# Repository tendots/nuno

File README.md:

# nuno
Electric fabric touchsensor module "nüno"

導電布タッチセンサーモジュールnünoのコードです。

質問や要望などあればこのページかFacebookページへご連絡ください。
* Facebook page https://www.facebook.com/Project-n%C3%BCno-183796265747425/

## 仕様 ##
* 静電容量タッチセンサ　[mtch6102](https://www.microchip.com/wwwproducts/en/MTCH6102)
* タッチチャンネル数8
* コネクタ GROVEコネクタ(I2C)

## 導線部接続方法

導線部（細長い方）は画像のように、縫い目がセンサー部（四角い方）の外縁に向くように接続してください。
逆につけた取り付けた場合、すべてのチャンネルの値が取得できません。

## フレキシブル基板コネクタ接続方法 ##

フレキシブル基板のコネクタは、リジット基板のFPCコネクタに接続後、
画像のようにフレキシブル基板と布を両方挟み込むようにして、
付属の固定具でネジ止めしてください。

## 付属ケースカット方法 ##

## 参考 ##
[touch_timer](https://github.com/theapi/touch_timer)

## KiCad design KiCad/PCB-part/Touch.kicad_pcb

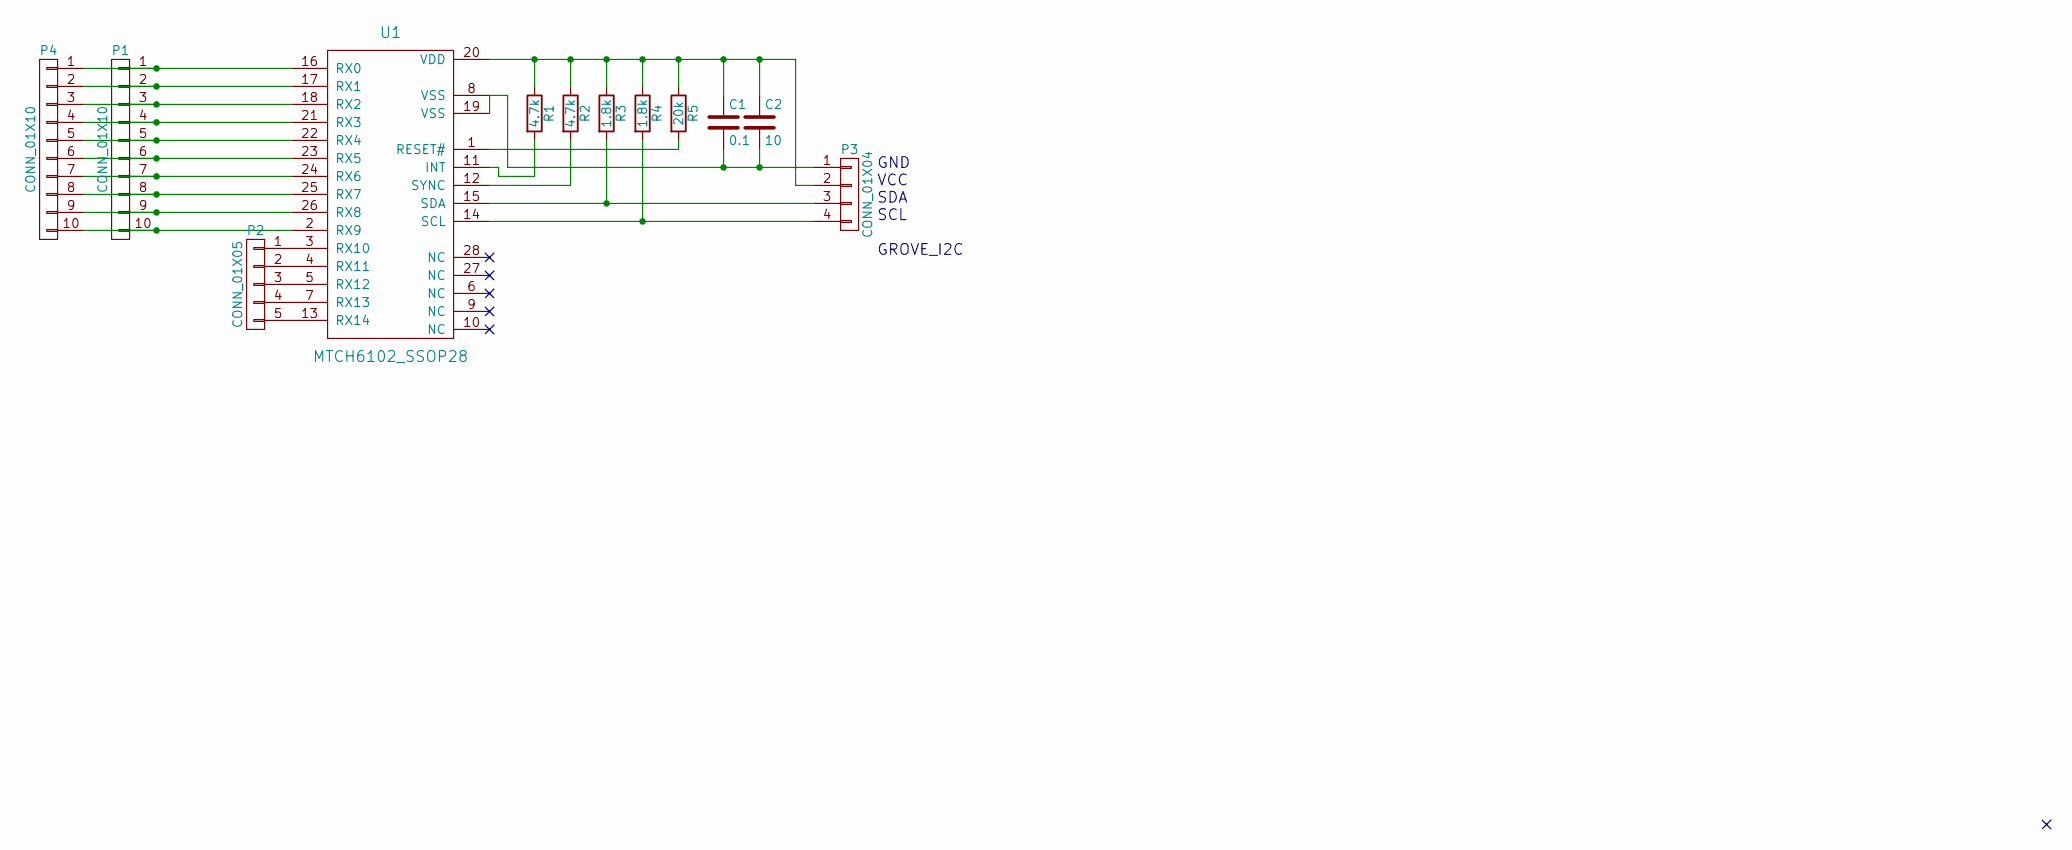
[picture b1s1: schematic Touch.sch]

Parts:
C1: 0.1; C_0603
C2: 10; C_0603
P1: CONN_01X10; Connector_Molex_PicoBlade_53047-1010
P2: CONN_01X05; Connector_Molex_PicoBlade_53047-0510
P3: CONN_01X04; Grove_I2C_Horisontal_4pin_2mmpitch
P4: CONN_01X10; FFC_CONNECTOR_1.0D-WTS-10P
R1, R2: 4.7k; R_0603
R3, R4: 1.8k; R_0603
R5: 20k; R_0603
U1: MTCH6102_SSOP28; SSOP-28_5.3x10.2mm_Pitch0.65mm

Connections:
unnamed: C1.1, C2.1, P3.2, R1.1, R2.1, R3.1, R4.1, R5.1, U1.20 (VDD)
unnamed: C1.2, C2.2, P3.1, U1.8 (VSS), U1.19 (VSS)
unnamed: P1.1, P4.1, U1.16 (RX0)
unnamed: P1.2, P4.2, U1.17 (RX1)
unnamed: P1.3, P4.3, U1.18 (RX2)
unnamed: P1.4, P4.4, U1.21 (RX3)
unnamed: P1.5, P4.5, U1.22 (RX4)
unnamed: P1.6, P4.6, U1.23 (RX5)
unnamed: P1.7, P4.7, U1.24 (RX6)
unnamed: P1.8, P4.8, U1.25 (RX7)
unnamed: P1.9, P4.9, U1.26 (RX8)
unnamed: P1.10, P4.10, U1.2 (RX9)
unnamed: P2.1, U1.3 (RX10)
unnamed: P2.2, U1.4 (RX11)
unnamed: P2.3, U1.5 (RX12)
unnamed: P2.4, U1.7 (RX13)
unnamed: P2.5, U1.13 (RX14)
unnamed: P3.3, R3.2, U1.15 (SDA)
unnamed: P3.4, R4.2, U1.14 (SCL)
unnamed: R1.2, U1.11 (INT)
unnamed: R2.2, U1.12 (SYNC)
unnamed: R5.2, U1.1 (RESET#)

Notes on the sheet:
GND VCC SDA SCL GROVE_I2C

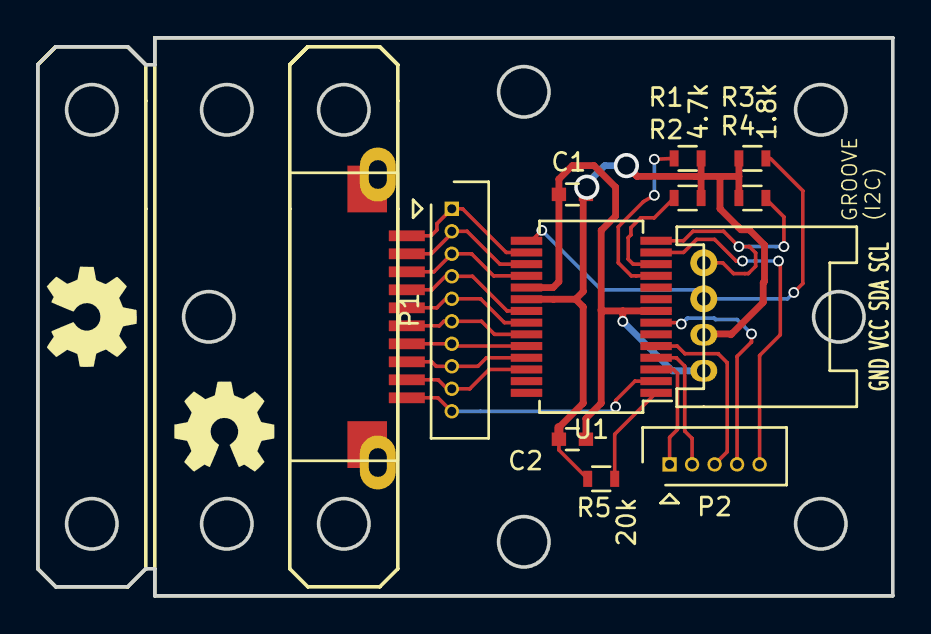
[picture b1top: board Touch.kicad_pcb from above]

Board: 2 copper layers, 47.5 x 31.0 mm, 14 parts (0 on the bottom side), 22 nets.

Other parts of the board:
OSHW: 1.1; OSHW_LOGL_SYLK_5mm
OSHW#2: 1.1; OSHW_LOGL_SYLK_5mm

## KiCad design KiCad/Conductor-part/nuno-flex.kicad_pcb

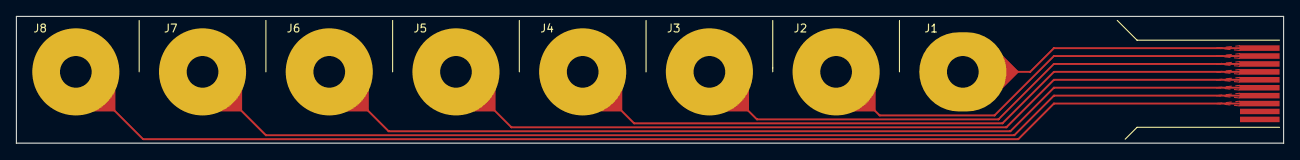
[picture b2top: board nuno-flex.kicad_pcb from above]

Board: 2 copper layers, 160.0 x 16.0 mm, 9 parts (0 on the bottom side), 8 nets.

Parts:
J1, J2, J3, J4, J5, J6, J7, J8: HOCK; Hock_4mm
J10: Conn_01x10; FPP_CONN_10

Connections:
unnamed: J1.1, J10.1
unnamed: J2.2, J10.2
unnamed: J3.3, J10.3
unnamed: J4.4, J10.4
unnamed: J5.5, J10.5
unnamed: J6.6, J10.6
unnamed: J7.7, J10.7
unnamed: J8.8, J10.8

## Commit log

2018-08-03 Create LICENSE
2018-08-03 M5Stack用サンプル
2018-08-03 KiCadファイルを追加
2018-08-03 仕様書を追加
2018-08-06 Update README.md
    導線部接続方法とフレキシブル基板コネクタ接続方法を追記
2018-08-21 Add PCB KiCad files
2018-09-07 仕様書aiファイルを削除
2018-10-08 MTCH6102.cppの反応を改善
2019-05-27 readRegisterがうまく動かないのを修正 リファクタリング実行
2019-05-28 Update graph
2021-04-26 nuno v2をM5Stack Core向けに修正
